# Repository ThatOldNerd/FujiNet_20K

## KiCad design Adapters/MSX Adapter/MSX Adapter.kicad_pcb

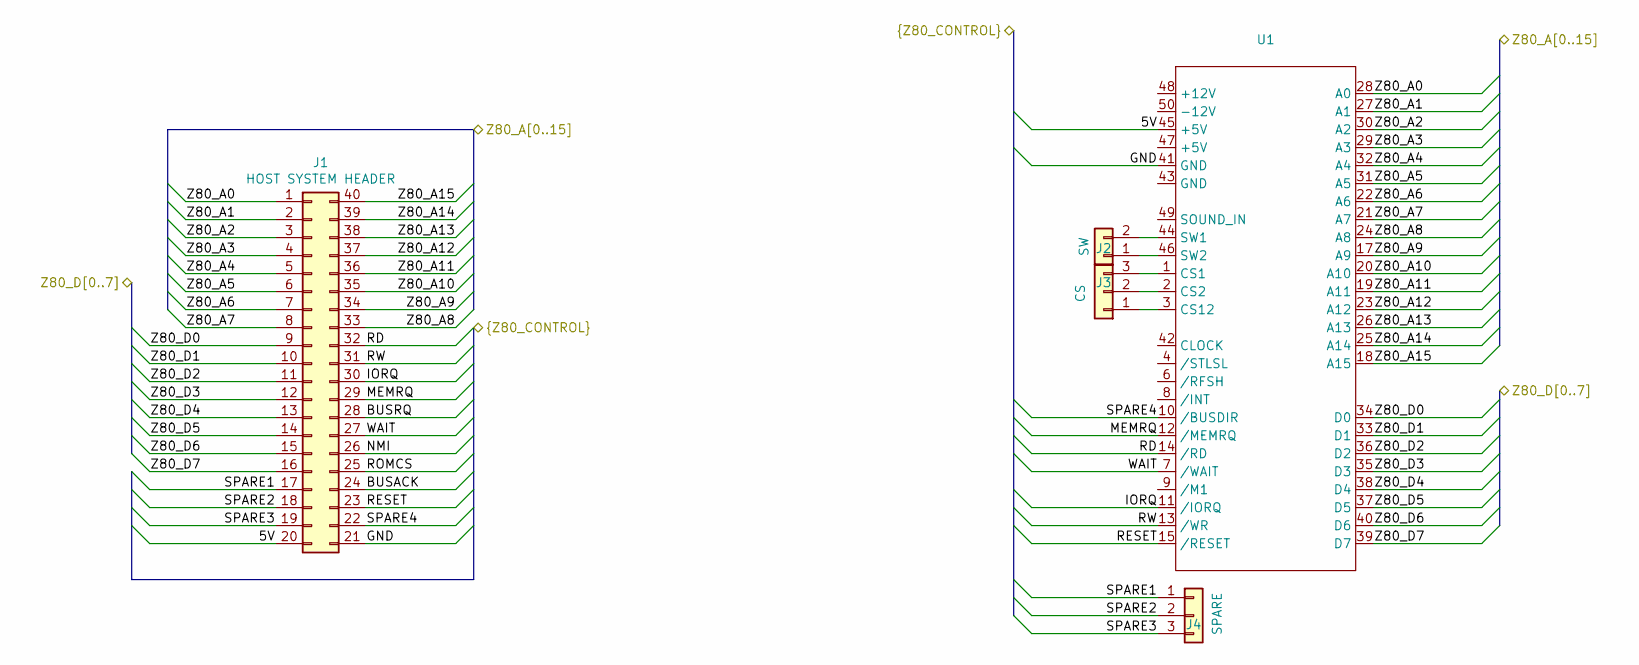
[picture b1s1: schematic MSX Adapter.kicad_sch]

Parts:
J1: HOST SYSTEM HEADER; PinHeader_2x20_P2.54mm_Vertical
J2: SW; PinHeader_1x02_P2.54mm_Vertical
J3: CS; PinHeader_1x03_P2.54mm_Vertical
J4: SPARE; PinHeader_1x03_P2.54mm_Vertical
U1: PinHeader_2x25_P2.54mm_Vertical

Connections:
/5V: J1.20, U1.45 (+5V)
/BUSACK: J1.24
/BUSRQ: J1.28
/GND: J1.21, U1.41 (GND)
/IORQ: J1.30, U1.11 (/IORQ)
/MEMRQ: J1.29, U1.12 (/MEMRQ)
/NMI: J1.26
/RD: J1.32, U1.14 (/RD)
/RESET: J1.23, U1.15 (/RESET)
/ROMCS: J1.25
/RW: J1.31, U1.13 (/WR)
/SPARE1: J1.17, J4.1
/SPARE2: J1.18, J4.2
/SPARE3: J1.19, J4.3
/SPARE4: J1.22, U1.10 (/BUSDIR)
/WAIT: J1.27, U1.7 (/WAIT)
/Z80_A0: J1.1, U1.28 (A0)
/Z80_A1: J1.2, U1.27 (A1)
/Z80_A2: J1.3, U1.30 (A2)
/Z80_A3: J1.4, U1.29 (A3)
/Z80_A4: J1.5, U1.32 (A4)
/Z80_A5: J1.6, U1.31 (A5)
/Z80_A6: J1.7, U1.22 (A6)
/Z80_A7: J1.8, U1.21 (A7)
/Z80_A8: J1.33, U1.24 (A8)
/Z80_A9: J1.34, U1.17 (A9)
/Z80_A10: J1.35, U1.20 (A10)
/Z80_A11: J1.36, U1.19 (A11)
/Z80_A12: J1.37, U1.23 (A12)
/Z80_A13: J1.38, U1.26 (A13)
/Z80_A14: J1.39, U1.25 (A14)
/Z80_A15: J1.40, U1.18 (A15)
/Z80_D0: J1.9, U1.34 (D0)
/Z80_D1: J1.10, U1.33 (D1)
/Z80_D2: J1.11, U1.36 (D2)
/Z80_D3: J1.12, U1.35 (D3)
/Z80_D4: J1.13, U1.38 (D4)
/Z80_D5: J1.14, U1.37 (D5)
/Z80_D6: J1.15, U1.40 (D6)
/Z80_D7: J1.16, U1.39 (D7)
unnamed: J2.1, U1.46 (SW2)
unnamed: J2.2, U1.44 (SW1)
unnamed: J3.1, U1.3 (CS12)
unnamed: J3.2, U1.2 (CS2)
unnamed: J3.3, U1.1 (CS1)

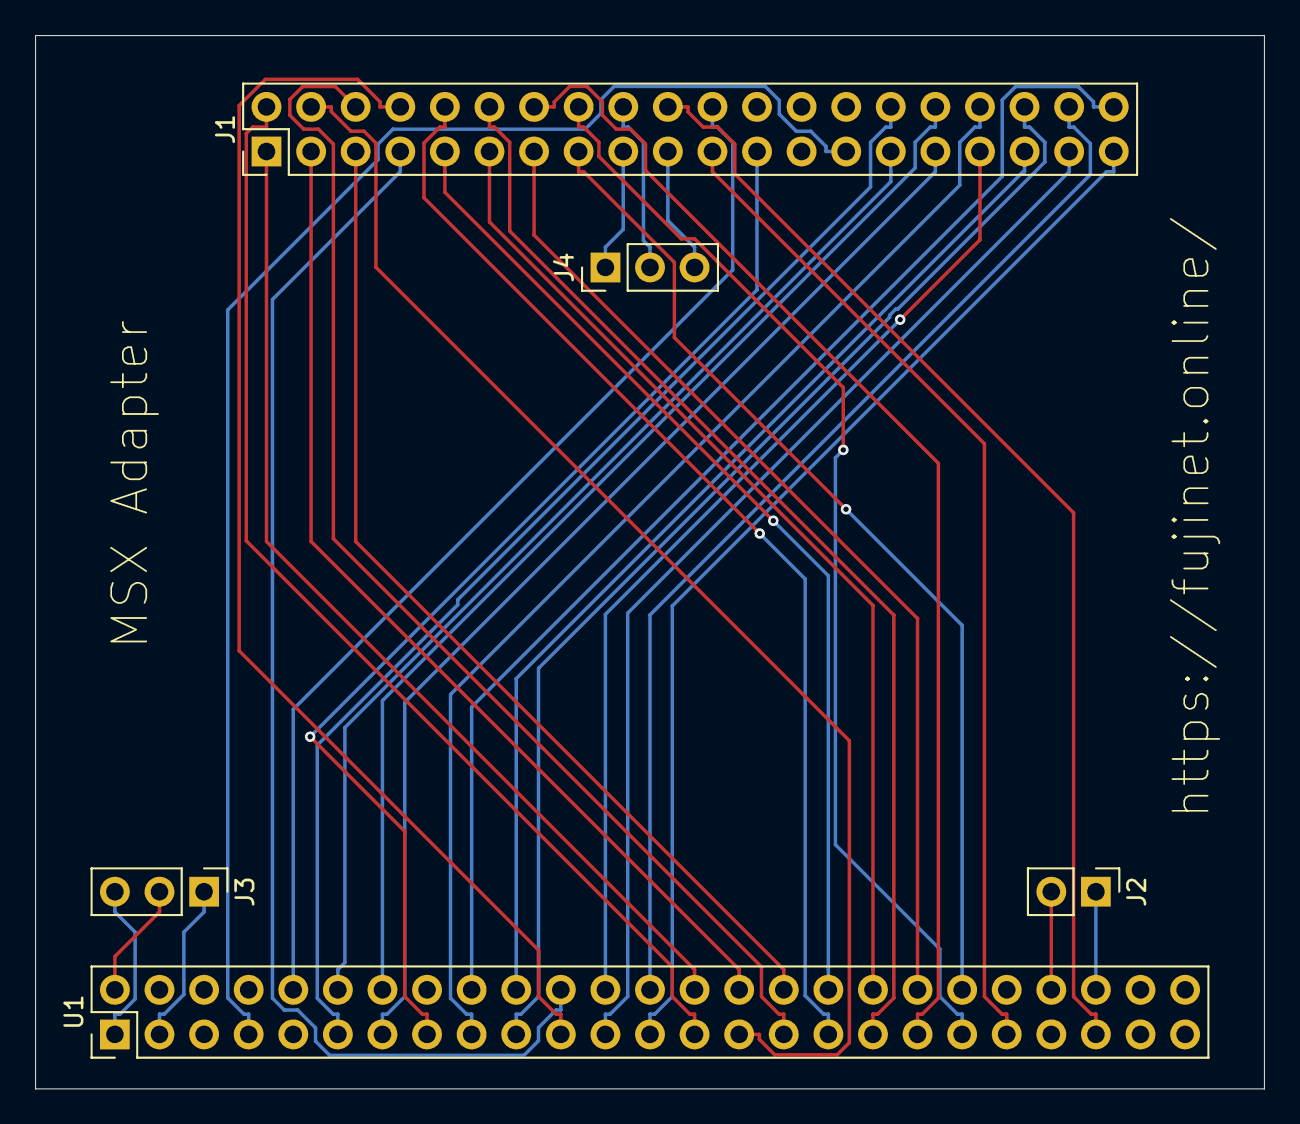
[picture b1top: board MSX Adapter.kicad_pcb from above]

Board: 2 copper layers, 70.0 x 60.0 mm, 5 parts (0 on the bottom side), 41 nets.

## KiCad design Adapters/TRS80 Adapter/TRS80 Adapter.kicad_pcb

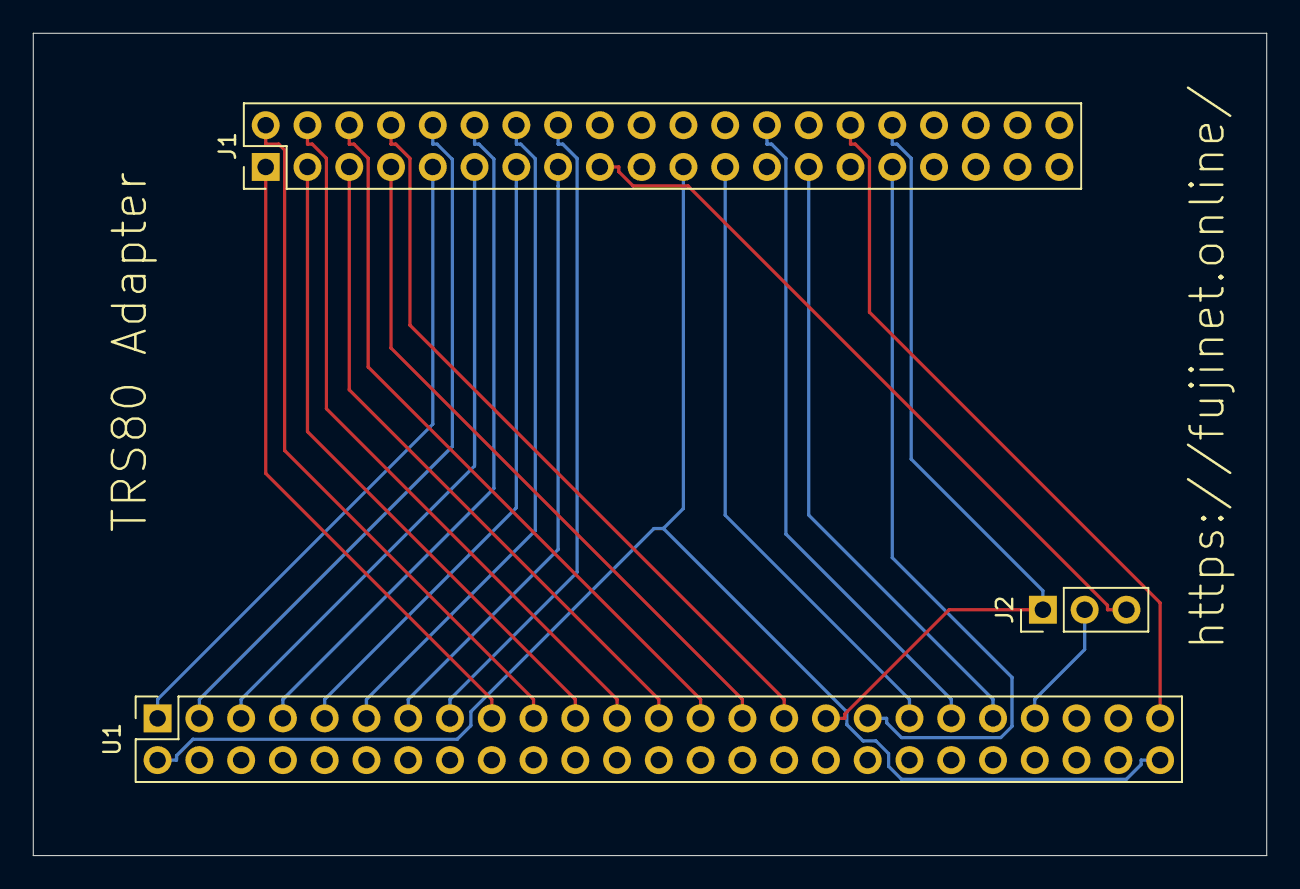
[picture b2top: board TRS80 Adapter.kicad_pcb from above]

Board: 2 copper layers, 75.0 x 50.0 mm, 3 parts (0 on the bottom side), 25 nets.

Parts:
J1: HOST SYSTEM HEADER; PinHeader_2x20_P2.54mm_Vertical
J2: EXT_IO_SEL; PinHeader_1x03_P2.54mm_Vertical
U1: PinSocket_2x25_P2.54mm_Vertical

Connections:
/GND: J1.21, U1.2 (GND), U1.50 (GND)
/IORQ: J1.30, U1.49 (IOREQ)
/NMI: J1.26, U1.39 (IO_BUS_INT)
/RD: J1.32, J2.1, U1.33 (IN)
/RESET: J1.23, U1.37 (RESET)
/RW: J1.31, U1.35 (OUT)
/SPARE1: J1.17, J2.3
/WAIT: J1.27, U1.41 (IO_BUS_WAIT)
/Z80_A0: J1.1, U1.17 (A0)
/Z80_A1: J1.2, U1.19 (A1)
/Z80_A2: J1.3, U1.21 (A2)
/Z80_A3: J1.4, U1.23 (A3)
/Z80_A4: J1.5, U1.25 (A4)
/Z80_A5: J1.6, U1.27 (A5)
/Z80_A6: J1.7, U1.29 (A6)
/Z80_A7: J1.8, U1.31 (A7)
/Z80_D0: J1.9, U1.1 (D0)
/Z80_D1: J1.10, U1.3 (D1)
/Z80_D2: J1.11, U1.5 (D2)
/Z80_D3: J1.12, U1.7 (D3)
/Z80_D4: J1.13, U1.9 (D4)
/Z80_D5: J1.14, U1.11 (D5)
/Z80_D6: J1.15, U1.13 (D6)
/Z80_D7: J1.16, U1.15 (D7)
unnamed: J2.2, U1.43 (EXT_IO_SEL)

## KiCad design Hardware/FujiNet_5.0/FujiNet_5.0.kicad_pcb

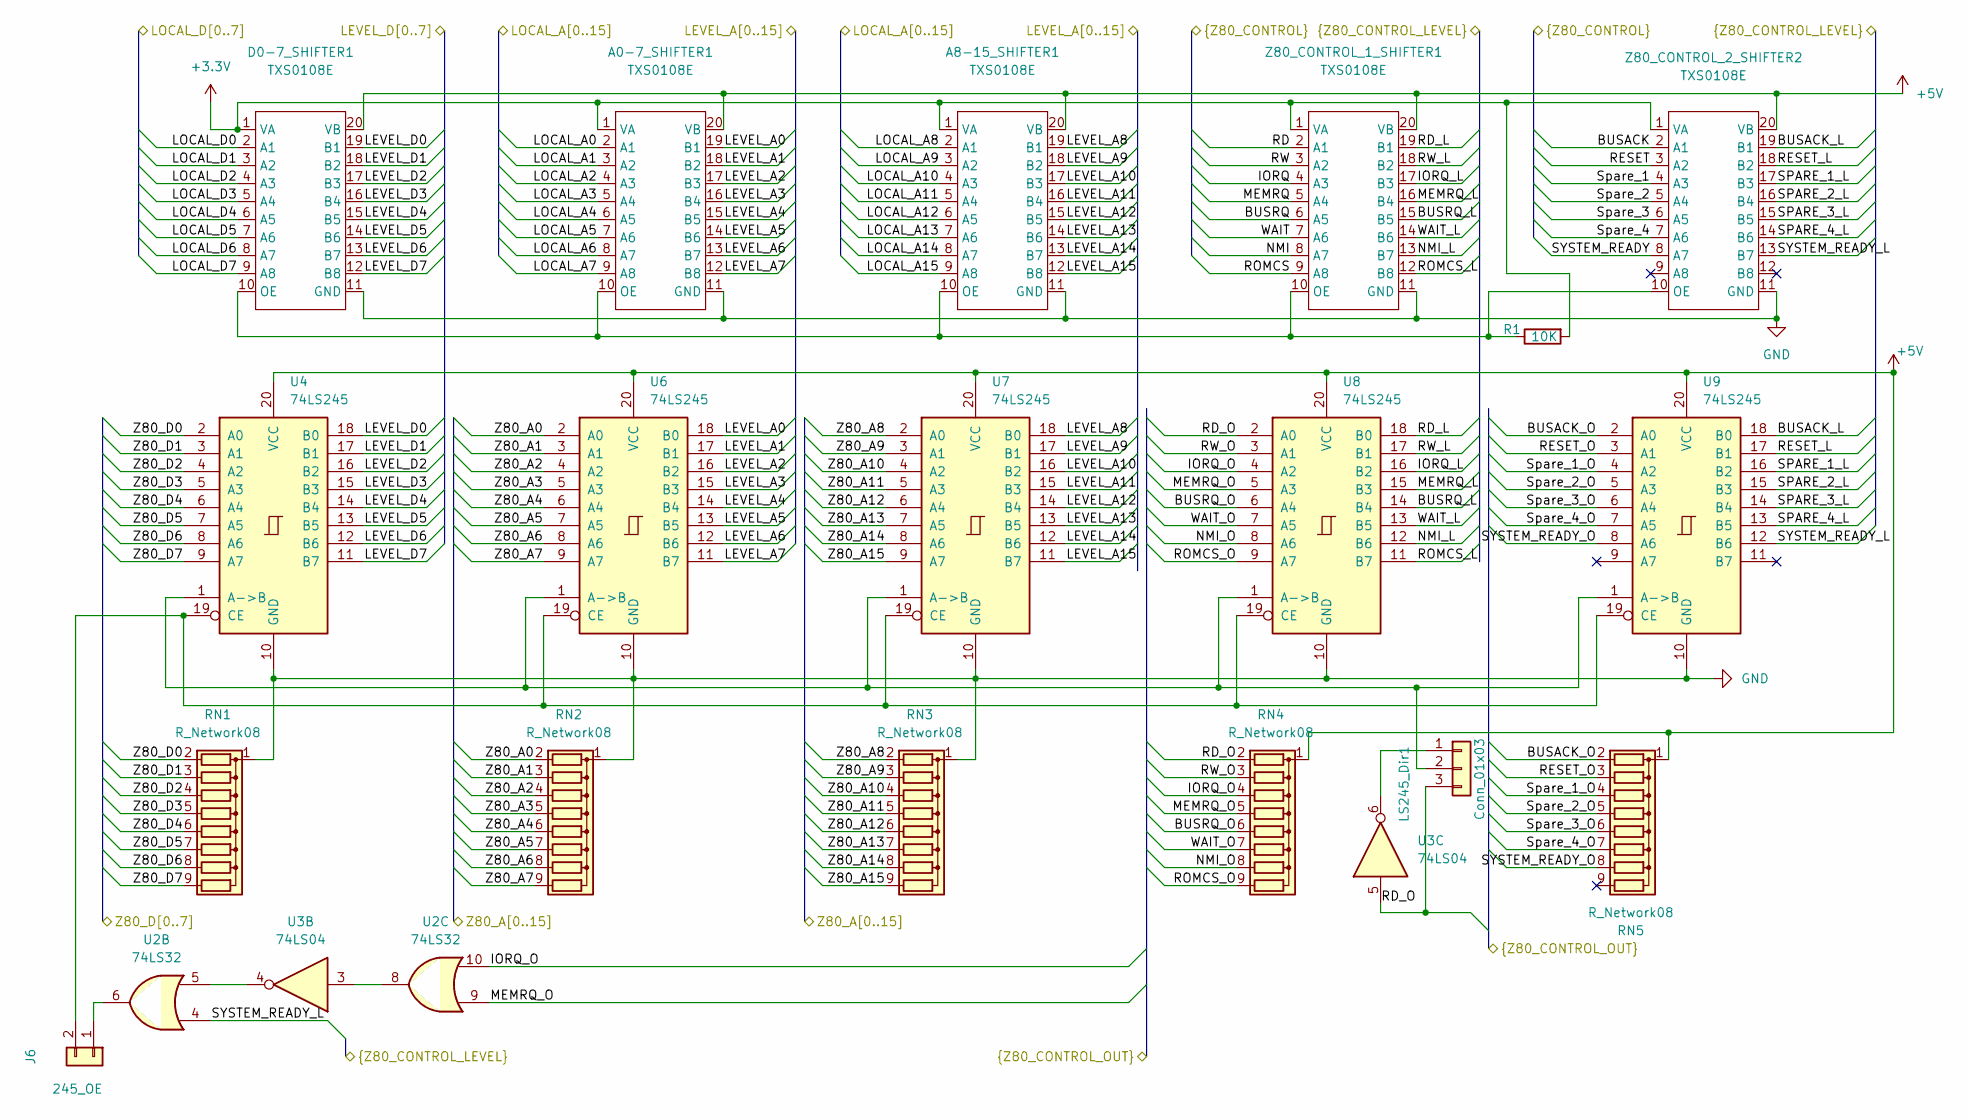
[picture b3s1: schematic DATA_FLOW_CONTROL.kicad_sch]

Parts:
A0-7_SHIFTER1, A8-15_SHIFTER1: TXS0108E; Adafruit_TXB010_ breakout_board
D0-7_SHIFTER1: TXS0108E; Adafruit_TXB010_ breakout_board
J6: 245_OE; PinHeader_1x02_P2.54mm_Vertical
LS245_Dir1: Conn_01x03; PinHeader_1x03_P2.54mm_Vertical
R1: 10K; R_Axial_DIN0207_L6.3mm_D2.5mm_P10.16mm_Horizontal
RN1, RN2, RN3, RN4, RN5: R_Network08; R_Array_SIP9
U2: 74LS32; DIP-14_W7.62mm_Socket
U3: 74LS04; DIP-14_W7.62mm_Socket
U4, U6, U7, U8, U9: 74LS245; DIP-20_W7.62mm_Socket
Z80_CONTROL_1_SHIFTER1, Z80_CONTROL_2_SHIFTER2: TXS0108E; Adafruit_TXB010_ breakout_board

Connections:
+3.3V: A0-7_SHIFTER1.1 (VA), A8-15_SHIFTER1.1 (VA), D0-7_SHIFTER1.1 (VA), R1.2, Z80_CONTROL_1_SHIFTER1.1 (VA), Z80_CONTROL_2_SHIFTER2.1 (VA); also elsewhere on the board
+5V: A0-7_SHIFTER1.20 (VB), A8-15_SHIFTER1.20 (VB), D0-7_SHIFTER1.20 (VB), RN4.1 (common), RN5.1 (common), U4.20 (VCC), U6.20 (VCC), U7.20 (VCC), U8.20 (VCC), U9.20 (VCC), Z80_CONTROL_1_SHIFTER1.20 (VB), Z80_CONTROL_2_SHIFTER2.20 (VB); also elsewhere on the board
/DATA FLOW CONTROL/BUSACK: Z80_CONTROL_2_SHIFTER2.2 (A1); also elsewhere on the board
/DATA FLOW CONTROL/BUSACK_L: U9.18 (B0), Z80_CONTROL_2_SHIFTER2.19 (B1); also elsewhere on the board
/DATA FLOW CONTROL/BUSACK_O: RN5.2 (R1), U9.2 (A0); also elsewhere on the board
/DATA FLOW CONTROL/BUSRQ: Z80_CONTROL_1_SHIFTER1.6 (A5); also elsewhere on the board
/DATA FLOW CONTROL/BUSRQ_L: U8.14 (B4), Z80_CONTROL_1_SHIFTER1.15 (B5)
/DATA FLOW CONTROL/BUSRQ_O: RN4.6 (R5), U8.6 (A4); also elsewhere on the board
/DATA FLOW CONTROL/IORQ: Z80_CONTROL_1_SHIFTER1.4 (A3); also elsewhere on the board
/DATA FLOW CONTROL/IORQ_L: U8.16 (B2), Z80_CONTROL_1_SHIFTER1.17 (B3)
/DATA FLOW CONTROL/IORQ_O: RN4.4 (R3), U2.10, U8.4 (A2); also elsewhere on the board
/DATA FLOW CONTROL/LEVEL_A0: A0-7_SHIFTER1.19 (B1), U6.18 (B0); also elsewhere on the board
/DATA FLOW CONTROL/LEVEL_A1: A0-7_SHIFTER1.18 (B2), U6.17 (B1); also elsewhere on the board
/DATA FLOW CONTROL/LEVEL_A2: A0-7_SHIFTER1.17 (B3), U6.16 (B2); also elsewhere on the board
/DATA FLOW CONTROL/LEVEL_A3: A0-7_SHIFTER1.16 (B4), U6.15 (B3); also elsewhere on the board
/DATA FLOW CONTROL/LEVEL_A4: A0-7_SHIFTER1.15 (B5), U6.14 (B4); also elsewhere on the board
/DATA FLOW CONTROL/LEVEL_A5: A0-7_SHIFTER1.14 (B6), U6.13 (B5); also elsewhere on the board
/DATA FLOW CONTROL/LEVEL_A6: A0-7_SHIFTER1.13 (B7), U6.12 (B6); also elsewhere on the board
/DATA FLOW CONTROL/LEVEL_A7: A0-7_SHIFTER1.12 (B8), U6.11 (B7); also elsewhere on the board
/DATA FLOW CONTROL/LEVEL_A8: A8-15_SHIFTER1.19 (B1), U7.18 (B0); also elsewhere on the board
/DATA FLOW CONTROL/LEVEL_A9: A8-15_SHIFTER1.18 (B2), U7.17 (B1); also elsewhere on the board
/DATA FLOW CONTROL/LEVEL_A10: A8-15_SHIFTER1.17 (B3), U7.16 (B2); also elsewhere on the board
/DATA FLOW CONTROL/LEVEL_A11: A8-15_SHIFTER1.16 (B4), U7.15 (B3); also elsewhere on the board
/DATA FLOW CONTROL/LEVEL_A12: A8-15_SHIFTER1.15 (B5), U7.14 (B4); also elsewhere on the board
/DATA FLOW CONTROL/LEVEL_A13: A8-15_SHIFTER1.14 (B6), U7.13 (B5); also elsewhere on the board
/DATA FLOW CONTROL/LEVEL_A14: A8-15_SHIFTER1.13 (B7), U7.12 (B6); also elsewhere on the board
/DATA FLOW CONTROL/LEVEL_A15: A8-15_SHIFTER1.12 (B8), U7.11 (B7); also elsewhere on the board
/DATA FLOW CONTROL/LEVEL_D0: D0-7_SHIFTER1.19 (B1), U4.18 (B0); also elsewhere on the board
/DATA FLOW CONTROL/LEVEL_D1: D0-7_SHIFTER1.18 (B2), U4.17 (B1); also elsewhere on the board
/DATA FLOW CONTROL/LEVEL_D2: D0-7_SHIFTER1.17 (B3), U4.16 (B2); also elsewhere on the board
/DATA FLOW CONTROL/LEVEL_D3: D0-7_SHIFTER1.16 (B4), U4.15 (B3); also elsewhere on the board
/DATA FLOW CONTROL/LEVEL_D4: D0-7_SHIFTER1.15 (B5), U4.14 (B4); also elsewhere on the board
/DATA FLOW CONTROL/LEVEL_D5: D0-7_SHIFTER1.14 (B6), U4.13 (B5); also elsewhere on the board
/DATA FLOW CONTROL/LEVEL_D6: D0-7_SHIFTER1.13 (B7), U4.12 (B6); also elsewhere on the board
/DATA FLOW CONTROL/LEVEL_D7: D0-7_SHIFTER1.12 (B8), U4.11 (B7); also elsewhere on the board
/DATA FLOW CONTROL/LOCAL_A0: A0-7_SHIFTER1.2 (A1); also elsewhere on the board
/DATA FLOW CONTROL/LOCAL_A1: A0-7_SHIFTER1.3 (A2); also elsewhere on the board
/DATA FLOW CONTROL/LOCAL_A2: A0-7_SHIFTER1.4 (A3); also elsewhere on the board
/DATA FLOW CONTROL/LOCAL_A3: A0-7_SHIFTER1.5 (A4); also elsewhere on the board
/DATA FLOW CONTROL/LOCAL_A4: A0-7_SHIFTER1.6 (A5); also elsewhere on the board
/DATA FLOW CONTROL/LOCAL_A5: A0-7_SHIFTER1.7 (A6); also elsewhere on the board
/DATA FLOW CONTROL/LOCAL_A6: A0-7_SHIFTER1.8 (A7); also elsewhere on the board
/DATA FLOW CONTROL/LOCAL_A7: A0-7_SHIFTER1.9 (A8); also elsewhere on the board
/DATA FLOW CONTROL/LOCAL_A8: A8-15_SHIFTER1.2 (A1); also elsewhere on the board
/DATA FLOW CONTROL/LOCAL_A9: A8-15_SHIFTER1.3 (A2); also elsewhere on the board
/DATA FLOW CONTROL/LOCAL_A10: A8-15_SHIFTER1.4 (A3); also elsewhere on the board
/DATA FLOW CONTROL/LOCAL_A11: A8-15_SHIFTER1.5 (A4); also elsewhere on the board
/DATA FLOW CONTROL/LOCAL_A12: A8-15_SHIFTER1.6 (A5); also elsewhere on the board
/DATA FLOW CONTROL/LOCAL_A13: A8-15_SHIFTER1.7 (A6); also elsewhere on the board
/DATA FLOW CONTROL/LOCAL_A14: A8-15_SHIFTER1.8 (A7); also elsewhere on the board
/DATA FLOW CONTROL/LOCAL_A15: A8-15_SHIFTER1.9 (A8); also elsewhere on the board
/DATA FLOW CONTROL/LOCAL_D0: D0-7_SHIFTER1.2 (A1); also elsewhere on the board
/DATA FLOW CONTROL/LOCAL_D1: D0-7_SHIFTER1.3 (A2); also elsewhere on the board
/DATA FLOW CONTROL/LOCAL_D2: D0-7_SHIFTER1.4 (A3); also elsewhere on the board
/DATA FLOW CONTROL/LOCAL_D3: D0-7_SHIFTER1.5 (A4); also elsewhere on the board
/DATA FLOW CONTROL/LOCAL_D4: D0-7_SHIFTER1.6 (A5); also elsewhere on the board
/DATA FLOW CONTROL/LOCAL_D5: D0-7_SHIFTER1.7 (A6); also elsewhere on the board
/DATA FLOW CONTROL/LOCAL_D6: D0-7_SHIFTER1.8 (A7); also elsewhere on the board
/DATA FLOW CONTROL/LOCAL_D7: D0-7_SHIFTER1.9 (A8); also elsewhere on the board
/DATA FLOW CONTROL/MEMRQ: Z80_CONTROL_1_SHIFTER1.5 (A4); also elsewhere on the board
/DATA FLOW CONTROL/MEMRQ_L: U8.15 (B3), Z80_CONTROL_1_SHIFTER1.16 (B4); also elsewhere on the board
/DATA FLOW CONTROL/MEMRQ_O: RN4.5 (R4), U2.9, U8.5 (A3); also elsewhere on the board
/DATA FLOW CONTROL/NMI: Z80_CONTROL_1_SHIFTER1.8 (A7); also elsewhere on the board
/DATA FLOW CONTROL/NMI_L: U8.12 (B6), Z80_CONTROL_1_SHIFTER1.13 (B7)
/DATA FLOW CONTROL/NMI_O: RN4.8 (R7), U8.8 (A6); also elsewhere on the board
/DATA FLOW CONTROL/RD: Z80_CONTROL_1_SHIFTER1.2 (A1); also elsewhere on the board
/DATA FLOW CONTROL/RD_L: U8.18 (B0), Z80_CONTROL_1_SHIFTER1.19 (B1); also elsewhere on the board
/DATA FLOW CONTROL/RD_O: LS245_Dir1.3, RN4.2 (R1), U3.5, U8.2 (A0); also elsewhere on the board
/DATA FLOW CONTROL/RESET: Z80_CONTROL_2_SHIFTER2.3 (A2); also elsewhere on the board
/DATA FLOW CONTROL/RESET_L: U9.17 (B1), Z80_CONTROL_2_SHIFTER2.18 (B2)
/DATA FLOW CONTROL/RESET_O: RN5.3 (R2), U9.3 (A1); also elsewhere on the board
/DATA FLOW CONTROL/ROMCS: Z80_CONTROL_1_SHIFTER1.9 (A8); also elsewhere on the board
/DATA FLOW CONTROL/ROMCS_L: U8.11 (B7), Z80_CONTROL_1_SHIFTER1.12 (B8); also elsewhere on the board
/DATA FLOW CONTROL/ROMCS_O: RN4.9 (R8), U8.9 (A7); also elsewhere on the board
/DATA FLOW CONTROL/RW: Z80_CONTROL_1_SHIFTER1.3 (A2); also elsewhere on the board
/DATA FLOW CONTROL/RW_L: U8.17 (B1), Z80_CONTROL_1_SHIFTER1.18 (B2); also elsewhere on the board
/DATA FLOW CONTROL/RW_O: RN4.3 (R2), U8.3 (A1); also elsewhere on the board
/DATA FLOW CONTROL/SPARE_1_L: U9.16 (B2), Z80_CONTROL_2_SHIFTER2.17 (B3)
/DATA FLOW CONTROL/SPARE_2_L: U9.15 (B3), Z80_CONTROL_2_SHIFTER2.16 (B4)
/DATA FLOW CONTROL/SPARE_3_L: U9.14 (B4), Z80_CONTROL_2_SHIFTER2.15 (B5)
/DATA FLOW CONTROL/SPARE_4_L: U9.13 (B5), Z80_CONTROL_2_SHIFTER2.14 (B6)
/DATA FLOW CONTROL/SYSTEM_READY: Z80_CONTROL_2_SHIFTER2.8 (A7); also elsewhere on the board
/DATA FLOW CONTROL/SYSTEM_READY_L: U2.4, U9.12 (B6), Z80_CONTROL_2_SHIFTER2.13 (B7)
/DATA FLOW CONTROL/SYSTEM_READY_O: RN5.8 (R7), U9.8 (A6)
/DATA FLOW CONTROL/Spare_1: Z80_CONTROL_2_SHIFTER2.4 (A3); also elsewhere on the board
/DATA FLOW CONTROL/Spare_1_O: RN5.4 (R3), U9.4 (A2); also elsewhere on the board
/DATA FLOW CONTROL/Spare_2: Z80_CONTROL_2_SHIFTER2.5 (A4); also elsewhere on the board
/DATA FLOW CONTROL/Spare_2_O: RN5.5 (R4), U9.5 (A3); also elsewhere on the board
/DATA FLOW CONTROL/Spare_3: Z80_CONTROL_2_SHIFTER2.6 (A5); also elsewhere on the board
/DATA FLOW CONTROL/Spare_3_O: RN5.6 (R5), U9.6 (A4); also elsewhere on the board
/DATA FLOW CONTROL/Spare_4: Z80_CONTROL_2_SHIFTER2.7 (A6); also elsewhere on the board
/DATA FLOW CONTROL/Spare_4_O: RN5.7 (R6), U9.7 (A5); also elsewhere on the board
/DATA FLOW CONTROL/WAIT: Z80_CONTROL_1_SHIFTER1.7 (A6); also elsewhere on the board
/DATA FLOW CONTROL/WAIT_L: U8.13 (B5), Z80_CONTROL_1_SHIFTER1.14 (B6)
/DATA FLOW CONTROL/WAIT_O: RN4.7 (R6), U8.7 (A5); also elsewhere on the board
/DATA FLOW CONTROL/Z80_A0: RN2.2 (R1), U6.2 (A0); also elsewhere on the board
/DATA FLOW CONTROL/Z80_A1: RN2.3 (R2), U6.3 (A1); also elsewhere on the board
/DATA FLOW CONTROL/Z80_A2: RN2.4 (R3), U6.4 (A2); also elsewhere on the board
/DATA FLOW CONTROL/Z80_A3: RN2.5 (R4), U6.5 (A3); also elsewhere on the board
/DATA FLOW CONTROL/Z80_A4: RN2.6 (R5), U6.6 (A4); also elsewhere on the board
/DATA FLOW CONTROL/Z80_A5: RN2.7 (R6), U6.7 (A5); also elsewhere on the board
/DATA FLOW CONTROL/Z80_A6: RN2.8 (R7), U6.8 (A6); also elsewhere on the board
/DATA FLOW CONTROL/Z80_A7: RN2.9 (R8), U6.9 (A7); also elsewhere on the board
/DATA FLOW CONTROL/Z80_A8: RN3.2 (R1), U7.2 (A0); also elsewhere on the board
/DATA FLOW CONTROL/Z80_A9: RN3.3 (R2), U7.3 (A1); also elsewhere on the board
/DATA FLOW CONTROL/Z80_A10: RN3.4 (R3), U7.4 (A2); also elsewhere on the board
/DATA FLOW CONTROL/Z80_A11: RN3.5 (R4), U7.5 (A3); also elsewhere on the board
/DATA FLOW CONTROL/Z80_A12: RN3.6 (R5), U7.6 (A4); also elsewhere on the board
/DATA FLOW CONTROL/Z80_A13: RN3.7 (R6), U7.7 (A5); also elsewhere on the board
/DATA FLOW CONTROL/Z80_A14: RN3.8 (R7), U7.8 (A6); also elsewhere on the board
/DATA FLOW CONTROL/Z80_A15: RN3.9 (R8), U7.9 (A7); also elsewhere on the board
/DATA FLOW CONTROL/Z80_D0: RN1.2 (R1), U4.2 (A0); also elsewhere on the board
/DATA FLOW CONTROL/Z80_D1: RN1.3 (R2), U4.3 (A1); also elsewhere on the board
/DATA FLOW CONTROL/Z80_D2: RN1.4 (R3), U4.4 (A2); also elsewhere on the board
/DATA FLOW CONTROL/Z80_D3: RN1.5 (R4), U4.5 (A3); also elsewhere on the board
/DATA FLOW CONTROL/Z80_D4: RN1.6 (R5), U4.6 (A4); also elsewhere on the board
/DATA FLOW CONTROL/Z80_D5: RN1.7 (R6), U4.7 (A5); also elsewhere on the board
/DATA FLOW CONTROL/Z80_D6: RN1.8 (R7), U4.8 (A6); also elsewhere on the board
/DATA FLOW CONTROL/Z80_D7: RN1.9 (R8), U4.9 (A7); also elsewhere on the board
GND: A0-7_SHIFTER1.11 (GND), A8-15_SHIFTER1.11 (GND), D0-7_SHIFTER1.11 (GND), RN1.1 (common), RN2.1 (common), RN3.1 (common), U4.10 (GND), U6.10 (GND), U7.10 (GND), U8.10 (GND), U9.10 (GND), Z80_CONTROL_1_SHIFTER1.11 (GND), Z80_CONTROL_2_SHIFTER2.11 (GND); also elsewhere on the board
unnamed: A0-7_SHIFTER1.10 (OE), A8-15_SHIFTER1.10 (OE), D0-7_SHIFTER1.10 (OE), R1.1, Z80_CONTROL_1_SHIFTER1.10 (OE), Z80_CONTROL_2_SHIFTER2.10 (OE)
unnamed: J6.1, U2.6
unnamed: J6.2, U4.19 (CE), U6.19 (CE), U7.19 (CE), U8.19 (CE), U9.19 (CE)
unnamed: LS245_Dir1.1, U3.6
unnamed: LS245_Dir1.2, U4.1 (A->B), U6.1 (A->B), U7.1 (A->B), U8.1 (A->B), U9.1 (A->B)
unnamed: U2.5, U3.4
unnamed: U2.8, U3.3

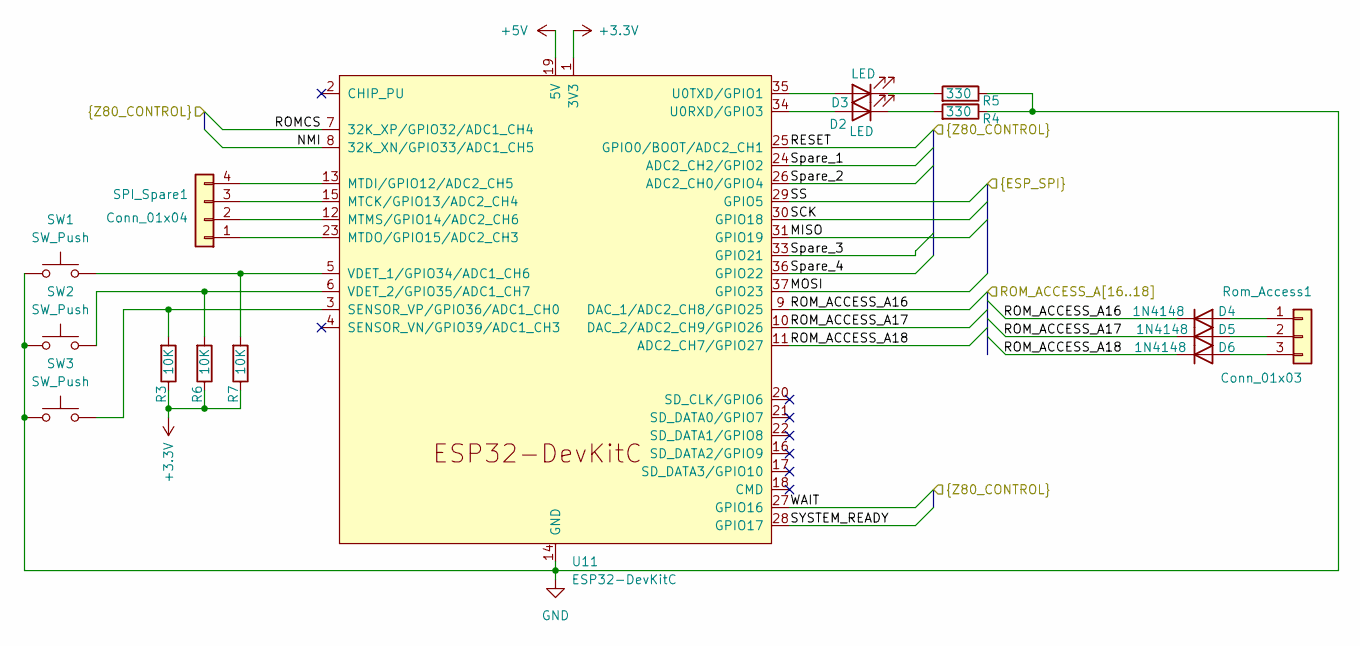
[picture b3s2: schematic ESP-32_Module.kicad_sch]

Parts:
D2, D3: LED; LED_D5.0mm
D4, D5, D6: 1N4148; D_DO-35_SOD27_P7.62mm_Horizontal
R3, R6, R7: 10K; R_Axial_DIN0207_L6.3mm_D2.5mm_P10.16mm_Horizontal
R4, R5: 330; R_Axial_DIN0207_L6.3mm_D2.5mm_P10.16mm_Horizontal
Rom_Access1: Conn_01x03; PinHeader_1x03_P2.54mm_Vertical
SPI_Spare1: Conn_01x04; PinHeader_1x04_P2.54mm_Vertical
SW1, SW2, SW3: SW_Push; SW_PUSH_6mm
U11: ESP32-DevKitC

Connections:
+3.3V: R3.1, R6.1, R7.1, U11.1 (3V3); also elsewhere on the board
+5V: U11.19 (5V); also elsewhere on the board
/DATA FLOW CONTROL/NMI: U11.8 (32K_XN/GPIO33/ADC1_CH5); also elsewhere on the board
/DATA FLOW CONTROL/RESET: U11.25 (GPIO0/BOOT/ADC2_CH1); also elsewhere on the board
/DATA FLOW CONTROL/ROMCS: U11.7 (32K_XP/GPIO32/ADC1_CH4); also elsewhere on the board
/DATA FLOW CONTROL/SYSTEM_READY: U11.28 (GPIO17); also elsewhere on the board
/DATA FLOW CONTROL/Spare_1: U11.24 (ADC2_CH2/GPIO2); also elsewhere on the board
/DATA FLOW CONTROL/Spare_2: U11.26 (ADC2_CH0/GPIO4); also elsewhere on the board
/DATA FLOW CONTROL/Spare_3: U11.33 (GPIO21); also elsewhere on the board
/DATA FLOW CONTROL/Spare_4: U11.36 (GPIO22); also elsewhere on the board
/DATA FLOW CONTROL/WAIT: U11.27 (GPIO16); also elsewhere on the board
/ESP-32 Module/MISO: U11.31 (GPIO19); also elsewhere on the board
/ESP-32 Module/MOSI: U11.37 (GPIO23); also elsewhere on the board
/ESP-32 Module/ROM_ACCESS_A16: D4.1 (K), U11.9 (DAC_1/ADC2_CH8/GPIO25); also elsewhere on the board
/ESP-32 Module/ROM_ACCESS_A17: D5.1 (K), U11.10 (DAC_2/ADC2_CH9/GPIO26); also elsewhere on the board
/ESP-32 Module/ROM_ACCESS_A18: D6.1 (K), U11.11 (ADC2_CH7/GPIO27); also elsewhere on the board
/ESP-32 Module/SCK: U11.30 (GPIO18); also elsewhere on the board
/ESP-32 Module/SS: U11.29 (GPIO5); also elsewhere on the board
GND: R4.1, R5.1, SW1.1, SW2.1, SW3.1, U11.14 (GND), U11.32 (GND), U11.38 (GND); also elsewhere on the board
unnamed: D2.2 (A), U11.34 (U0RXD/GPIO3)
unnamed: D2.1 (K), R4.2
unnamed: D3.2 (A), U11.35 (U0TXD/GPIO1)
unnamed: D3.1 (K), R5.2
unnamed: D4.2 (A), Rom_Access1.1
unnamed: D5.2 (A), Rom_Access1.2
unnamed: D6.2 (A), Rom_Access1.3
unnamed: SPI_Spare1.1, U11.23 (MTDO/GPIO15/ADC2_CH3)
unnamed: SPI_Spare1.2, U11.12 (MTMS/GPIO14/ADC2_CH6)
unnamed: SPI_Spare1.3, U11.15 (MTCK/GPIO13/ADC2_CH4)
unnamed: SPI_Spare1.4, U11.13 (MTDI/GPIO12/ADC2_CH5)
unnamed: R3.2, SW3.2, U11.3 (SENSOR_VP/GPIO36/ADC1_CH0)
unnamed: R7.2, SW1.2, U11.5 (VDET_1/GPIO34/ADC1_CH6)
unnamed: R6.2, SW2.2, U11.6 (VDET_2/GPIO35/ADC1_CH7)

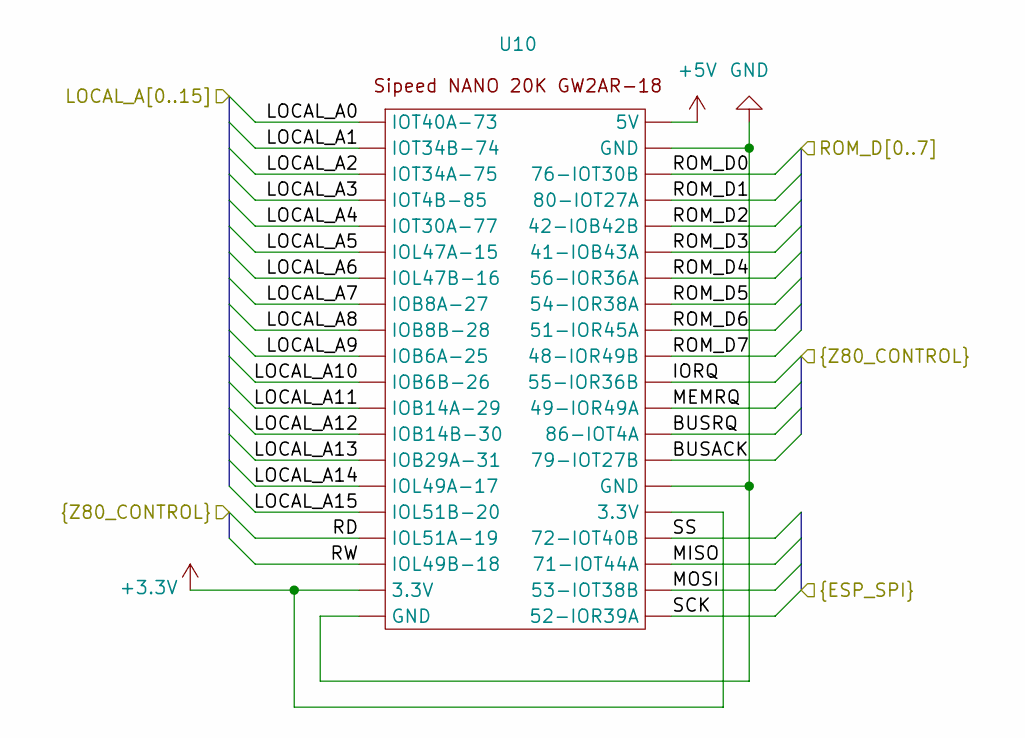
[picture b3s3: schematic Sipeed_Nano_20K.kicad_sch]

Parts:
U10: Sipeed Tang Nano 20k

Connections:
+3.3V: U10.16 (3.3V), U10.22 (3.3V); also elsewhere on the board
+5V: U10.1 (5V); also elsewhere on the board
/DATA FLOW CONTROL/BUSACK: U10.14 (79-IOT27B); also elsewhere on the board
/DATA FLOW CONTROL/BUSRQ: U10.13 (86-IOT4A); also elsewhere on the board
/DATA FLOW CONTROL/IORQ: U10.11 (55-IOR36B); also elsewhere on the board
/DATA FLOW CONTROL/LOCAL_A0: U10.40 (IOT40A-73); also elsewhere on the board
/DATA FLOW CONTROL/LOCAL_A1: U10.39 (IOT34B-74); also elsewhere on the board
/DATA FLOW CONTROL/LOCAL_A2: U10.38 (IOT34A-75); also elsewhere on the board
/DATA FLOW CONTROL/LOCAL_A3: U10.37 (IOT4B-85); also elsewhere on the board
/DATA FLOW CONTROL/LOCAL_A4: U10.36 (IOT30A-77); also elsewhere on the board
/DATA FLOW CONTROL/LOCAL_A5: U10.35 (IOL47A-15); also elsewhere on the board
/DATA FLOW CONTROL/LOCAL_A6: U10.34 (IOL47B-16); also elsewhere on the board
/DATA FLOW CONTROL/LOCAL_A7: U10.33 (IOB8A-27); also elsewhere on the board
/DATA FLOW CONTROL/LOCAL_A8: U10.32 (IOB8B-28); also elsewhere on the board
/DATA FLOW CONTROL/LOCAL_A9: U10.31 (IOB6A-25); also elsewhere on the board
/DATA FLOW CONTROL/LOCAL_A10: U10.30 (IOB6B-26); also elsewhere on the board
/DATA FLOW CONTROL/LOCAL_A11: U10.29 (IOB14A-29); also elsewhere on the board
/DATA FLOW CONTROL/LOCAL_A12: U10.28 (IOB14B-30); also elsewhere on the board
/DATA FLOW CONTROL/LOCAL_A13: U10.27 (IOB29A-31); also elsewhere on the board
/DATA FLOW CONTROL/LOCAL_A14: U10.26 (IOL49A-17); also elsewhere on the board
/DATA FLOW CONTROL/LOCAL_A15: U10.25 (IOL51B-20); also elsewhere on the board
/DATA FLOW CONTROL/LOCAL_D0: U10.3 (76-IOT30B); also elsewhere on the board
/DATA FLOW CONTROL/LOCAL_D1: U10.4 (80-IOT27A); also elsewhere on the board
/DATA FLOW CONTROL/LOCAL_D2: U10.5 (42-IOB42B); also elsewhere on the board
/DATA FLOW CONTROL/LOCAL_D3: U10.6 (41-IOB43A); also elsewhere on the board
/DATA FLOW CONTROL/LOCAL_D4: U10.7 (56-IOR36A); also elsewhere on the board
/DATA FLOW CONTROL/LOCAL_D5: U10.8 (54-IOR38A); also elsewhere on the board
/DATA FLOW CONTROL/LOCAL_D6: U10.9 (51-IOR45A); also elsewhere on the board
/DATA FLOW CONTROL/LOCAL_D7: U10.10 (48-IOR49B); also elsewhere on the board
/DATA FLOW CONTROL/MEMRQ: U10.12 (49-IOR49A); also elsewhere on the board
/DATA FLOW CONTROL/RD: U10.24 (IOL51A-19); also elsewhere on the board
/DATA FLOW CONTROL/RW: U10.23 (IOL49B-18); also elsewhere on the board
/ESP-32 Module/MISO: U10.18 (71-IOT44A); also elsewhere on the board
/ESP-32 Module/MOSI: U10.19 (53-IOT38B); also elsewhere on the board
/ESP-32 Module/SCK: U10.20 (52-IOR39A); also elsewhere on the board
/ESP-32 Module/SS: U10.17 (72-IOT40B); also elsewhere on the board
GND: U10.2 (GND), U10.15 (GND), U10.21 (GND); also elsewhere on the board

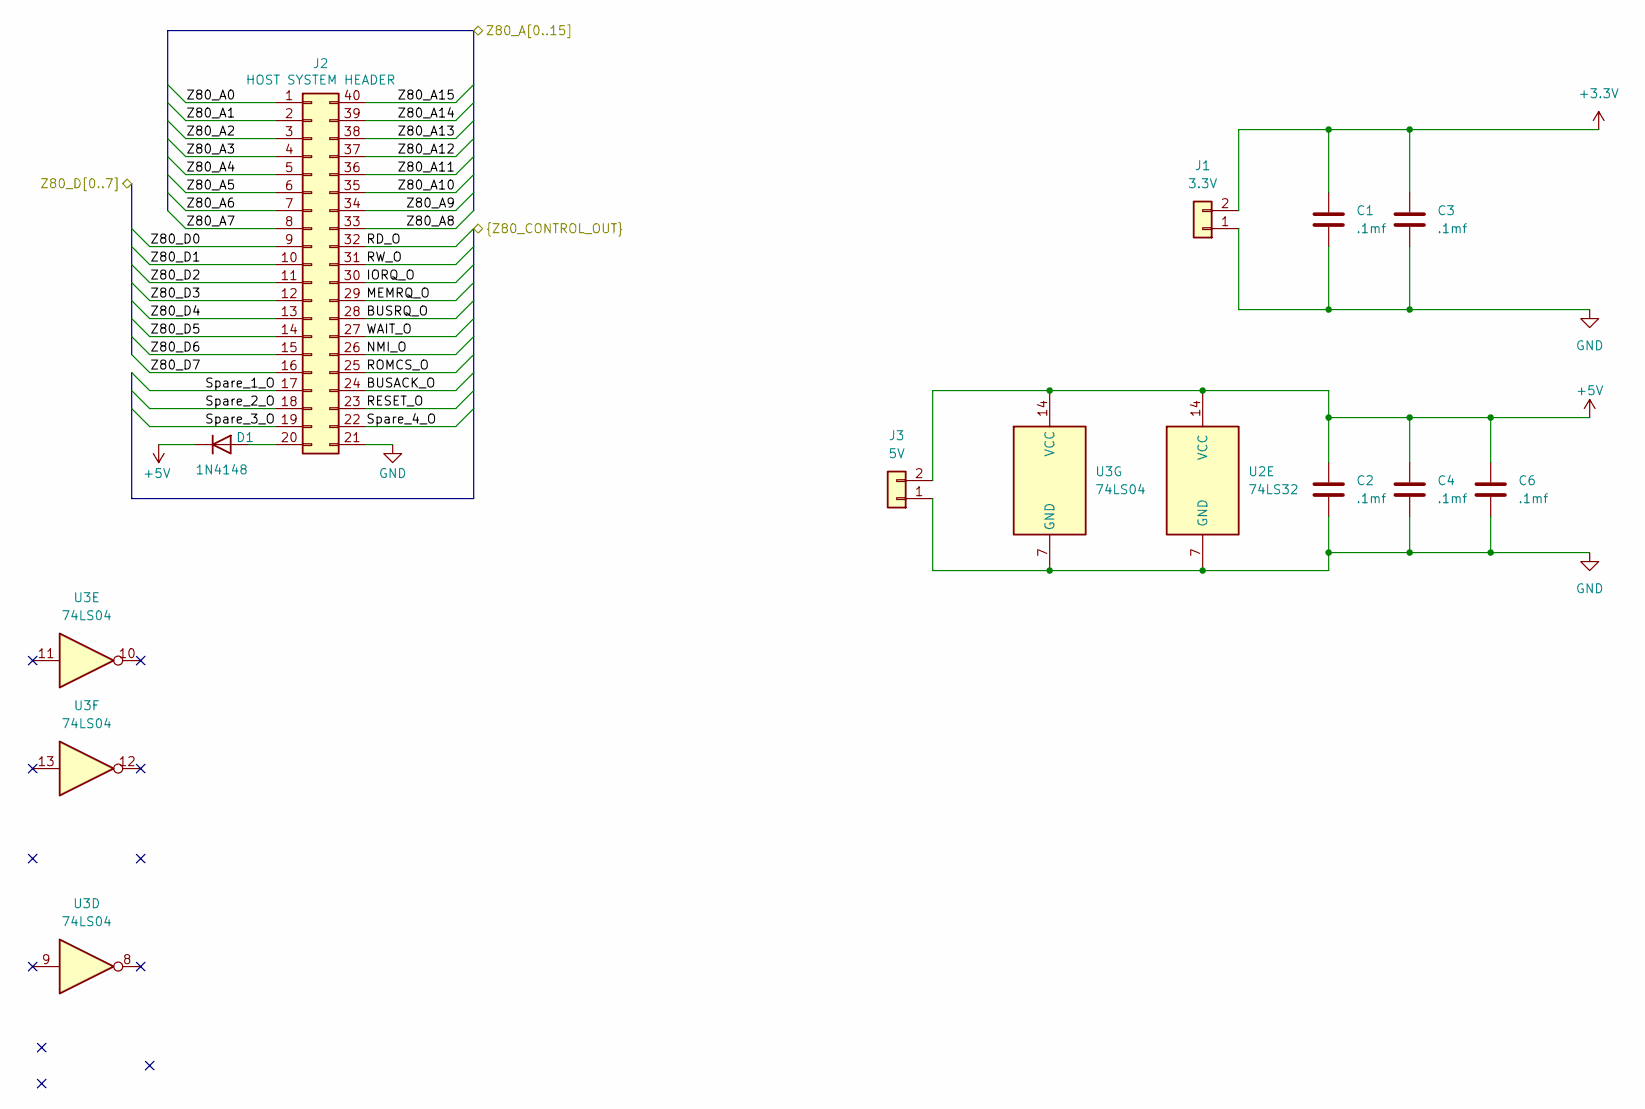
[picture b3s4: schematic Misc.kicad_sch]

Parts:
C1, C2, C3, C4, C6: .1mf; C_Disc_D7.5mm_W2.5mm_P5.00mm
D1: 1N4148; D_DO-35_SOD27_P7.62mm_Horizontal
J1: 3.3V; PinHeader_1x02_P2.54mm_Vertical
J2: HOST SYSTEM HEADER; PinHeader_2x20_P2.54mm_Vertical
J3: 5V; PinHeader_1x02_P2.54mm_Vertical
U2: 74LS32; DIP-14_W7.62mm_Socket
U3: 74LS04; DIP-14_W7.62mm_Socket

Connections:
+3.3V: C1.1, C3.1, J1.2; also elsewhere on the board
+5V: C2.1, C4.1, C6.1, D1.1 (K), J3.2, U2.14 (VCC), U3.14 (VCC); also elsewhere on the board
/DATA FLOW CONTROL/BUSACK_O: J2.24; also elsewhere on the board
/DATA FLOW CONTROL/BUSRQ_O: J2.28; also elsewhere on the board
/DATA FLOW CONTROL/IORQ_O: J2.30; also elsewhere on the board
/DATA FLOW CONTROL/MEMRQ_O: J2.29; also elsewhere on the board
/DATA FLOW CONTROL/NMI_O: J2.26; also elsewhere on the board
/DATA FLOW CONTROL/RD_O: J2.32; also elsewhere on the board
/DATA FLOW CONTROL/RESET_O: J2.23; also elsewhere on the board
/DATA FLOW CONTROL/ROMCS_O: J2.25; also elsewhere on the board
/DATA FLOW CONTROL/RW_O: J2.31; also elsewhere on the board
/DATA FLOW CONTROL/Spare_1_O: J2.17; also elsewhere on the board
/DATA FLOW CONTROL/Spare_2_O: J2.18; also elsewhere on the board
/DATA FLOW CONTROL/Spare_3_O: J2.19; also elsewhere on the board
/DATA FLOW CONTROL/Spare_4_O: J2.22; also elsewhere on the board
/DATA FLOW CONTROL/WAIT_O: J2.27; also elsewhere on the board
/DATA FLOW CONTROL/Z80_A0: J2.1; also elsewhere on the board
/DATA FLOW CONTROL/Z80_A1: J2.2; also elsewhere on the board
/DATA FLOW CONTROL/Z80_A2: J2.3; also elsewhere on the board
/DATA FLOW CONTROL/Z80_A3: J2.4; also elsewhere on the board
/DATA FLOW CONTROL/Z80_A4: J2.5; also elsewhere on the board
/DATA FLOW CONTROL/Z80_A5: J2.6; also elsewhere on the board
/DATA FLOW CONTROL/Z80_A6: J2.7; also elsewhere on the board
/DATA FLOW CONTROL/Z80_A7: J2.8; also elsewhere on the board
/DATA FLOW CONTROL/Z80_A8: J2.33; also elsewhere on the board
/DATA FLOW CONTROL/Z80_A9: J2.34; also elsewhere on the board
/DATA FLOW CONTROL/Z80_A10: J2.35; also elsewhere on the board
/DATA FLOW CONTROL/Z80_A11: J2.36; also elsewhere on the board
/DATA FLOW CONTROL/Z80_A12: J2.37; also elsewhere on the board
/DATA FLOW CONTROL/Z80_A13: J2.38; also elsewhere on the board
/DATA FLOW CONTROL/Z80_A14: J2.39; also elsewhere on the board
/DATA FLOW CONTROL/Z80_A15: J2.40; also elsewhere on the board
/DATA FLOW CONTROL/Z80_D0: J2.9; also elsewhere on the board
/DATA FLOW CONTROL/Z80_D1: J2.10; also elsewhere on the board
/DATA FLOW CONTROL/Z80_D2: J2.11; also elsewhere on the board
/DATA FLOW CONTROL/Z80_D3: J2.12; also elsewhere on the board
/DATA FLOW CONTROL/Z80_D4: J2.13; also elsewhere on the board
/DATA FLOW CONTROL/Z80_D5: J2.14; also elsewhere on the board
/DATA FLOW CONTROL/Z80_D6: J2.15; also elsewhere on the board
/DATA FLOW CONTROL/Z80_D7: J2.16; also elsewhere on the board
GND: C1.2, C2.2, C3.2, C4.2, C6.2, J1.1, J2.21, J3.1, U2.7 (GND), U3.7 (GND); also elsewhere on the board
unnamed: D1.2 (A), J2.20
